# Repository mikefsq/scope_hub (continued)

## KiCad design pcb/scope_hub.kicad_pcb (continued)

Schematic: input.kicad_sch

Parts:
C206, C210: 100nF; C_0603_1608Metric; LCSC C14663
C207, C209: 100nF; C_0402_1005Metric; LCSC C1525
C208: 1uF; C_0603_1608Metric; LCSC C5199872
D8: SMBJ16CA; D_SMB; MPN SMBJ16CA; LCSC C151255
F1: 15A; Fuse_2410_6125Metric_JDT; LCSC C2994767
J11: PJ-080BH; BarrelJack_CUI_PJ-080BH_Horizontal; MPN PJ-080BH; LCSC C3094242
Q7: NCEP40T11G; PowerPAK_SO-8_Single; LCSC C182465
R115, R117: 10R; R_0603_1608Metric; LCSC C22859
R116: 1mR; R_2512_6332Metric; LCSC C5375452
U55: LM74700-Q1; SOT-23-6; MPN LM74700QDBVRQ1; LCSC C2941042
U56: INA226; TSSOP-10_3x3mm_P0.5mm; MPN INA226AIDGSR; LCSC C49851

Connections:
+3V3: C207.1, U56.1 (A1), U56.6 (VS); also elsewhere on the board
+12V: C210.1, F1.2; also elsewhere on the board
/I2C0_SCL: U56.5 (SCL); also elsewhere on the board
/I2C0_SDA: U56.2 (A0), U56.4 (SDA); also elsewhere on the board
/Input 12V/VIN_PROT: Q7.5 (D), R115.1, R116.1, U55.4 (CATHODE), U56.8 (Vbus)
/Input 12V/VIN_RAW: C206.1, C208.1, D8.1 (K), J11.1, Q7.1 (S), Q7.2 (S), Q7.3 (S), U55.3 (EN), U55.6 (ANODE)
GND: C206.2, C207.2, C210.2, D8.2 (A), J11.2, J11.3, U55.2 (GND), U56.7 (GND); also elsewhere on the board
unnamed: F1.1, R116.2, R117.1
unnamed: Q7.4 (G), U55.5 (GATE)
unnamed: C208.2, U55.1 (VCAP)
unnamed: C209.1, R115.2, U56.10 (Vin+)
unnamed: C209.2, R117.2, U56.9 (Vin-)

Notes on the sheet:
INA226 at 0x46 (A1=VS, A0=SDA)

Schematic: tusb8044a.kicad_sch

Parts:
C78: 1uF; C_0402_1005Metric; LCSC C52923
C79, C108: 10uF; C_0805_2012Metric; LCSC C15850
C80, C85: 18pF; C_0402_1005Metric; LCSC C1549
C81, C82, C88, C89, C95, C96, C102, C103, C109: 0.001uF; C_0402_1005Metric; LCSC C1523
C83, C84, C90, C91, C98, C99, C104, C105, C110: 0.01uF; C_0402_1005Metric; LCSC C15195
C86, C87, C92, C93, C94, C100, C101, C106, C107, C111: 0.1uF; C_0402_1005Metric; LCSC C1525
R43, R45, R46, R52: 1K; R_0402_1005Metric; LCSC C11702
R44: 1M; R_0402_1005Metric; LCSC C26083
R47: 9.53K; R_0402_1005Metric; LCSC C96273
R48: 10K; R_0402_1005Metric; LCSC C25744
R49: 90.9K; R_0402_1005Metric; LCSC C26989
R50, R53, R54: 4.7K; R_0402_1005Metric; LCSC C25900
R51: NOPOP; R_0402_1005Metric; not fitted
R55, R56, R57: 4.7K DNI; R_0402_1005Metric; LCSC C25900; not fitted
U21: AT24C08C; SOIC-8_3.9x4.9mm_P1.27mm; LCSC C31422
U22: TUSB8044A; QFN-64-1EP_9x9mm_P0.5mm_EP6x6mm_ThermalVias; MPN TUSB8044ARGCR; LCSC C2678041
Y2: 24MHz; Crystal_SMD_3225-4Pin_3.2x2.5mm; LCSC C362340

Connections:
+1V1: C79.1, C82.1, C84.1, C87.1, C89.1, C91.1, C93.1, C96.1, C99.1, C101.1, C103.1, C105.1, C107.1, C108.1, C109.1, C110.1, C111.1, U22.5 (VDD), U22.8 (VDD), U22.13 (VDD), U22.21 (VDD), U22.28 (VDD), U22.31 (VDD), U22.51 (VDD), U22.57 (VDD); also elsewhere on the board
+3V3: C78.1, C81.1, C83.1, C86.1, C88.1, C90.1, C92.1, C94.1, C95.1, C98.1, C100.1, C102.1, C104.1, C106.1, R51.1, R53.1, R54.1, R55.1, R56.1, R57.1, U21.8 (VCC), U22.16 (VDD33), U22.34 (VDD33), U22.52 (VDD33), U22.63 (VDD33); also elsewhere on the board
/DN4_D_N: U22.2 (USB_DM_DN1); also elsewhere on the board
/DN4_D_P: U22.1 (USB_DP_DN1); also elsewhere on the board
/DN5_D_N: U22.10 (USB_DM_DN2); also elsewhere on the board
/DN5_D_P: U22.9 (USB_DP_DN2); also elsewhere on the board
/DN6_D_N: U22.18 (USB_DM_DN3); also elsewhere on the board
/DN6_D_P: U22.17 (USB_DP_DN3); also elsewhere on the board
/DN Port 4/OVERCUR_N: U22.46 (OVERCUR1z); also elsewhere on the board
/DN Port 4/SSRX_N: U22.7 (USB_SSRXM_DN1); also elsewhere on the board
/DN Port 4/SSRX_P: U22.6 (USB_SSRXP_DN1); also elsewhere on the board
/DN Port 4/SSTX_N: U22.4 (USB_SSTXM_DN1); also elsewhere on the board
/DN Port 4/SSTX_P: U22.3 (USB_SSTXP_DN1); also elsewhere on the board
/DN Port 5/OVERCUR_N: U22.47 (OVERCUR2z); also elsewhere on the board
/DN Port 5/SSRX_N: U22.15 (USB_SSRXM_DN2); also elsewhere on the board
/DN Port 5/SSRX_P: U22.14 (USB_SSRXP_DN2); also elsewhere on the board
/DN Port 5/SSTX_N: U22.12 (USB_SSTXM_DN2); also elsewhere on the board
/DN Port 5/SSTX_P: U22.11 (USB_SSTXP_DN2); also elsewhere on the board
/DN Port 6 (5A)/OVERCUR_N: U22.44 (OVERCUR3z); also elsewhere on the board
/DN Port 6 (5A)/SSRX_N: U22.23 (USB_SSRXM_DN3); also elsewhere on the board
/DN Port 6 (5A)/SSRX_P: U22.22 (USB_SSRXP_DN3); also elsewhere on the board
/DN Port 6 (5A)/SSTX_N: U22.20 (USB_SSTXM_DN3); also elsewhere on the board
/DN Port 6 (5A)/SSTX_P: U22.19 (USB_SSTXP_DN3); also elsewhere on the board
/LB_N: U22.59 (USB_SSRXM_UP); also elsewhere on the board
/LB_P: U22.58 (USB_SSRXP_UP); also elsewhere on the board
/LC_N: U22.56 (USB_SSTXM_UP); also elsewhere on the board
/LC_P: U22.55 (USB_SSTXP_UP); also elsewhere on the board
/LNK_D_N: U22.54 (USB_DM_UP); also elsewhere on the board
/LNK_D_P: U22.53 (USB_DP_UP); also elsewhere on the board
/PICO_D_N: U22.25 (USB_DM_DN4); also elsewhere on the board
/PICO_D_P: U22.24 (USB_DP_DN4); also elsewhere on the board
/RAILS_READY: U22.50 (GRSTz); also elsewhere on the board
/TUSB8044A Hub1/OVERCUR4Z: U22.43 (OVERCUR4z)
/TUSB8044A Hub1/PWRON1_BATEN1: R55.2, U22.36 (PWRCTL1/BATEN1); also elsewhere on the board
/TUSB8044A Hub1/PWRON2_BATEN2: R56.2, U22.35 (PWRCTL2/BATEN2); also elsewhere on the board
/TUSB8044A Hub1/PWRON3_BATEN3: R57.2, U22.33 (PWRCTL3/BATEN3); also elsewhere on the board
/TUSB8044A Hub1/PWRON4_BATEN4: U22.32 (PWRCTL4/BATEN4)
/TUSB8044A Hub1/SCL_SMBCLK: R53.2, U21.6 (SCL), U22.38 (SCL/SMBCLK)
/TUSB8044A Hub1/SDA_SMBDAT: R54.2, U21.5 (SDA), U22.37 (SDA/SMBDAT)
/TUSB8044A Hub1/TEST_TRSTZ: R50.1, U22.49 (TEST)
/TUSB8044A Hub1/USB_R1: R47.1, U22.64 (USB_R1)
/TUSB8044A Hub1/USB_SSRXM_DN4: U22.30 (USB_SSRXM_DN4)
/TUSB8044A Hub1/USB_SSRXP_DN4: U22.29 (USB_SSRXP_DN4)
/TUSB8044A Hub1/USB_SSTXM_DN4: U22.27 (USB_SSTXM_DN4)
/TUSB8044A Hub1/USB_SSTXP_DN4: U22.26 (USB_SSTXP_DN4)
/TUSB8044A Hub1/USB_VBUS: R48.1, R49.1, U22.48 (USB_VBUS)
/TUSB8044A Hub1/XI: C85.1, R44.2, U22.62 (XI), Y2.3
/TUSB8044A Hub1/XO: C80.1, R44.1, U22.61 (XO), Y2.1
/UP_VBUS: R49.2; also elsewhere on the board
GND: C78.2, C79.2, C80.2, C81.2, C82.2, C83.2, C84.2, C85.2, C86.2, C87.2, C88.2, C89.2, C90.2, C91.2, C92.2, C93.2, C94.2, C95.2, C96.2, C98.2, C99.2, C100.2, C101.2, C102.2, C103.2, C104.2, C105.2, C106.2, C107.2, C108.2, C109.2, C110.2, C111.2, R43.2, R45.2, R46.2, R47.2, R48.2, R50.2, R52.2, U21.4 (GND), U22.65 (VSS), Y2.2 (G), Y2.4 (G); also elsewhere on the board
unnamed: R43.1, U21.1 (A0)
unnamed: R45.1, U21.2 (A1)
unnamed: R46.1, U21.3 (A2)
unnamed: R51.2, R52.1, U21.7 (WP)

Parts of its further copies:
C5: 1uF; C_0402_1005Metric; LCSC C52923
C6, C35: 10uF; C_0805_2012Metric; LCSC C15850
C7, C12: 18pF; C_0402_1005Metric; LCSC C1549
C8, C9, C15, C16, C22, C23, C29, C30, C36: 0.001uF; C_0402_1005Metric; LCSC C1523
C10, C11, C17, C18, C25, C26, C31, C32, C37: 0.01uF; C_0402_1005Metric; LCSC C15195
C13, C14, C19, C20, C21, C27, C28, C33, C34, C38: 0.1uF; C_0402_1005Metric; LCSC C1525
R1, R3, R4, R10: 1K; R_0402_1005Metric; LCSC C11702
R2: 1M; R_0402_1005Metric; LCSC C26083
R5: 9.53K; R_0402_1005Metric; LCSC C96273
R6: 10K; R_0402_1005Metric; LCSC C25744
R7: 90.9K; R_0402_1005Metric; LCSC C26989
R8, R11, R12: 4.7K; R_0402_1005Metric; LCSC C25900
R9: NOPOP; R_0402_1005Metric; not fitted
R13, R14, R15: 4.7K DNI; R_0402_1005Metric; LCSC C25900; not fitted
U1: AT24C08C; SOIC-8_3.9x4.9mm_P1.27mm; LCSC C31422
U2: TUSB8044A; QFN-64-1EP_9x9mm_P0.5mm_EP6x6mm_ThermalVias; MPN TUSB8044ARGCR; LCSC C2678041
Y1: 24MHz; Crystal_SMD_3225-4Pin_3.2x2.5mm; LCSC C362340

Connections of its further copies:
+1V1: C6.1, C9.1, C11.1, C14.1, C16.1, C18.1, C20.1, C23.1, C26.1, C28.1, C30.1, C32.1, C34.1, C35.1, C36.1, C37.1, C38.1, U2.5 (VDD), U2.8 (VDD), U2.13 (VDD), U2.21 (VDD), U2.28 (VDD), U2.31 (VDD), U2.51 (VDD), U2.57 (VDD); also elsewhere on the board
+3V3: C5.1, C8.1, C10.1, C13.1, C15.1, C17.1, C19.1, C21.1, C22.1, C25.1, C27.1, C29.1, C31.1, C33.1, R9.1, R11.1, R12.1, R13.1, R14.1, R15.1, U1.8 (VCC), U2.16 (VDD33), U2.34 (VDD33), U2.52 (VDD33), U2.63 (VDD33); also elsewhere on the board
/DN1_D_N: U2.2 (USB_DM_DN1); also elsewhere on the board
/DN1_D_P: U2.1 (USB_DP_DN1); also elsewhere on the board
/DN2_D_N: U2.10 (USB_DM_DN2); also elsewhere on the board
/DN2_D_P: U2.9 (USB_DP_DN2); also elsewhere on the board
/DN3_D_N: U2.18 (USB_DM_DN3); also elsewhere on the board
/DN3_D_P: U2.17 (USB_DP_DN3); also elsewhere on the board
/DN Port 1/OVERCUR_N: U2.46 (OVERCUR1z); also elsewhere on the board
/DN Port 1/SSRX_N: U2.7 (USB_SSRXM_DN1); also elsewhere on the board
/DN Port 1/SSRX_P: U2.6 (USB_SSRXP_DN1); also elsewhere on the board
/DN Port 1/SSTX_N: U2.4 (USB_SSTXM_DN1); also elsewhere on the board
/DN Port 1/SSTX_P: U2.3 (USB_SSTXP_DN1); also elsewhere on the board
/DN Port 2/OVERCUR_N: U2.47 (OVERCUR2z); also elsewhere on the board
/DN Port 2/SSRX_N: U2.15 (USB_SSRXM_DN2); also elsewhere on the board
/DN Port 2/SSRX_P: U2.14 (USB_SSRXP_DN2); also elsewhere on the board
/DN Port 2/SSTX_N: U2.12 (USB_SSTXM_DN2); also elsewhere on the board
/DN Port 2/SSTX_P: U2.11 (USB_SSTXP_DN2); also elsewhere on the board
/DN Port 3/OVERCUR_N: U2.44 (OVERCUR3z); also elsewhere on the board
/DN Port 3/SSRX_N: U2.23 (USB_SSRXM_DN3); also elsewhere on the board
/DN Port 3/SSRX_P: U2.22 (USB_SSRXP_DN3); also elsewhere on the board
/DN Port 3/SSTX_N: U2.20 (USB_SSTXM_DN3); also elsewhere on the board
/DN Port 3/SSTX_P: U2.19 (USB_SSTXP_DN3); also elsewhere on the board
/LA_N: U2.27 (USB_SSTXM_DN4); also elsewhere on the board
/LA_P: U2.26 (USB_SSTXP_DN4); also elsewhere on the board
/LD_N: U2.30 (USB_SSRXM_DN4); also elsewhere on the board
/LD_P: U2.29 (USB_SSRXP_DN4); also elsewhere on the board
/LNK_D_N: U2.25 (USB_DM_DN4); also elsewhere on the board
/LNK_D_P: U2.24 (USB_DP_DN4); also elsewhere on the board
/RAILS_READY: U2.50 (GRSTz); also elsewhere on the board
/SCL_SMBCLK: R11.2, U1.6 (SCL), U2.38 (SCL/SMBCLK)
/SDA_SMBDAT: R12.2, U1.5 (SDA), U2.37 (SDA/SMBDAT)
/TUSB8044A Hub/OVERCUR4Z: U2.43 (OVERCUR4z)
/TUSB8044A Hub/PWRON1_BATEN1: R13.2, U2.36 (PWRCTL1/BATEN1); also elsewhere on the board
/TUSB8044A Hub/PWRON2_BATEN2: R14.2, U2.35 (PWRCTL2/BATEN2); also elsewhere on the board
/TUSB8044A Hub/PWRON3_BATEN3: R15.2, U2.33 (PWRCTL3/BATEN3); also elsewhere on the board
/TUSB8044A Hub/PWRON4_BATEN4: U2.32 (PWRCTL4/BATEN4)
/TUSB8044A Hub/TEST_TRSTZ: R8.1, U2.49 (TEST)
/TUSB8044A Hub/USB_R1: R5.1, U2.64 (USB_R1)
/TUSB8044A Hub/USB_VBUS: R6.1, R7.1, U2.48 (USB_VBUS)
/TUSB8044A Hub/XI: C12.1, R2.2, U2.62 (XI), Y1.3
/TUSB8044A Hub/XO: C7.1, R2.1, U2.61 (XO), Y1.1
/UP_D_N: U2.54 (USB_DM_UP); also elsewhere on the board
/UP_D_P: U2.53 (USB_DP_UP); also elsewhere on the board
/UP_SSRX_N: U2.59 (USB_SSRXM_UP); also elsewhere on the board
/UP_SSRX_P: U2.58 (USB_SSRXP_UP); also elsewhere on the board
/UP_SSTX_N: U2.56 (USB_SSTXM_UP); also elsewhere on the board
/UP_SSTX_P: U2.55 (USB_SSTXP_UP); also elsewhere on the board
/UP_VBUS: R7.2; also elsewhere on the board
GND: C5.2, C6.2, C7.2, C8.2, C9.2, C10.2, C11.2, C12.2, C13.2, C14.2, C15.2, C16.2, C17.2, C18.2, C19.2, C20.2, C21.2, C22.2, C23.2, C25.2, C26.2, C27.2, C28.2, C29.2, C30.2, C31.2, C32.2, C33.2, C34.2, C35.2, C36.2, C37.2, C38.2, R1.2, R3.2, R4.2, R5.2, R6.2, R8.2, R10.2, U1.4 (GND), U2.65 (VSS), Y1.2 (G), Y1.4 (G); also elsewhere on the board
unnamed: R1.1, U1.1 (A0)
unnamed: R3.1, U1.2 (A1)
unnamed: R4.1, U1.3 (A2)
unnamed: R9.2, R10.1, U1.7 (WP)

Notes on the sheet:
24 MHz CLOCK
RAIL FILTERING AND DECOUPLING
UPSTREAM VBUS DETECT (divider good to 11.4V)
REF RESISTOR / RESET / TEST
hub HID-to-I2C master
OPTIONAL EEPROM CIRCUITRY

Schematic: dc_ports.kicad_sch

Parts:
C211, C212, C213, C214, C215, C216, C217, C218: 10uF; C_1210_3225Metric; LCSC C386166
C219, C220, C221, C222, C223, C224: 100nF; C_0603_1608Metric; LCSC C14663
C233: 100nF; C_0402_1005Metric; LCSC C1525
D9, D10, D11, D12, D13, D14: LED red; LED_0603_1608Metric; LCSC C2286
J12, J13, J14, J15, J16, J17: 2 Conductors, 3 Contacts; BarrelJack_CUI_PJ-063AH_Horizontal; MPN PJ-063AH; LCSC C22434582
R118, R119: 2.2K; R_0402_1005Metric; LCSC C25879
R120: 10 mOhms; RC2010N_VIS; MPN LRAM20DFER010; LCSC C22470460
R121, R122, R123, R124, R125: 20 mOhms; R_1206_3216Metric; MPN FMF06FTHR020-LH; LCSC C371097
R126, R127, R128, R129, R130, R131: 330; R_0402_1005Metric; LCSC C25104
U57: PCA9685BS; QFN-28-1EP_6x6mm_P0.65mm_EP4.25x4.25mm; MPN PCA9685BS,118; LCSC C5191634

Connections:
+3V3: C233.2, D9.2 (A), D10.2 (A), D11.2 (A), D12.2 (A), D13.2 (A), D14.2 (A), R118.1, R119.1, U57.21 (A5), U57.25 (VDD); also elsewhere on the board
+12V: C211.1, C212.1; also elsewhere on the board
/DC Ports/Vout0: C213.1, C219.1, J12.1, R120.2; also elsewhere on the board
/DC Ports/Vout0_EN: U57.3 (LED0); also elsewhere on the board
/DC Ports/Vout0_HS: R120.1; also elsewhere on the board
/DC Ports/Vout0_LED: R126.2, U57.4 (LED1)
/DC Ports/Vout1: C214.1, C220.1, J13.1, R121.2; also elsewhere on the board
/DC Ports/Vout1_EN: U57.5 (LED2); also elsewhere on the board
/DC Ports/Vout1_HS: R121.1; also elsewhere on the board
/DC Ports/Vout1_LED: R127.2, U57.6 (LED3)
/DC Ports/Vout2: C215.1, C221.1, J14.1, R122.2; also elsewhere on the board
/DC Ports/Vout2_EN: U57.7 (LED4); also elsewhere on the board
/DC Ports/Vout2_HS: R122.1; also elsewhere on the board
/DC Ports/Vout2_LED: R128.2, U57.8 (LED5)
/DC Ports/Vout3: C216.1, C222.1, J15.1, R123.2; also elsewhere on the board
/DC Ports/Vout3_EN: U57.9 (LED6); also elsewhere on the board
/DC Ports/Vout3_HS: R123.1; also elsewhere on the board
/DC Ports/Vout3_LED: R129.2, U57.10 (LED7)
/DC Ports/Vout4: C217.1, C223.1, J16.1, R124.2; also elsewhere on the board
/DC Ports/Vout4_EN: U57.12 (LED8); also elsewhere on the board
/DC Ports/Vout4_HS: R124.1; also elsewhere on the board
/DC Ports/Vout4_LED: R130.2, U57.13 (LED9)
/DC Ports/Vout5: C218.1, C224.1, J17.1, R125.2; also elsewhere on the board
/DC Ports/Vout5_EN: U57.14 (LED10); also elsewhere on the board
/DC Ports/Vout5_HS: R125.1; also elsewhere on the board
/DC Ports/Vout5_LED: R131.2, U57.15 (LED11)
/I2C0_SCL: R118.2, U57.23 (SCL); also elsewhere on the board
/I2C0_SDA: R119.2, U57.24 (SDA); also elsewhere on the board
/USBLED_12: U57.16 (LED12); also elsewhere on the board
/USBLED_34: U57.17 (LED13); also elsewhere on the board
/USBLED_56: U57.18 (LED14); also elsewhere on the board
/USBLED_UP: U57.19 (LED15); also elsewhere on the board
GND: C211.2, C212.2, C213.2, C214.2, C215.2, C216.2, C217.2, C218.2, C219.2, C220.2, C221.2, C222.2, C223.2, C224.2, C233.1, J12.2, J12.3, J13.2, J13.3, J14.2, J14.3, J15.2, J15.3, J16.2, J16.3, J17.2, J17.3, U57.1 (A3), U57.2 (A4), U57.11 (VSS), U57.20 (~OE), U57.22 (EXTCLK), U57.26 (A0), U57.27 (A1), U57.28 (A2), U57.29 (VSS); also elsewhere on the board
unnamed: D9.1 (K), R126.1
unnamed: D10.1 (K), R127.1
unnamed: D11.1 (K), R128.1
unnamed: D12.1 (K), R129.1
unnamed: D13.1 (K), R130.1
unnamed: D14.1 (K), R131.1

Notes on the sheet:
AUX2
DEW2
Focuser
DEW1
0x42
TEC
I2c Address = 0x40 + A[5:0]
C194/C195: 25 V X5R 0805, place at the switch group
0x40
0x45
All Call Address 0x70
0x41
0x44
AUX1
0x43

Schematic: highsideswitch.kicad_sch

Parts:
R137: 499R; R_0402_1005Metric; LCSC C4125
U67: High Side N-Channel On/Off; PWP0014F_N; MPN TPS1H100AQPWPRQ1; LCSC C478465

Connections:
+12V: U67.8 (VS), U67.9 (VS), U67.10 (VS); also elsewhere on the board
/DC Ports/Vout4_EN: U67.3 (IN); also elsewhere on the board
/DC Ports/Vout4_HS: U67.5 (OUT), U67.6 (OUT), U67.7 (OUT); also elsewhere on the board
/DC Ports/Vout4_ST: U67.14 (ST_N)
GND: R137.2, U67.2 (GND), U67.12 (DIAG_EN), U67.15 (PAD); also elsewhere on the board
unnamed: R137.1, U67.13 (CL)

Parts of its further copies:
R133, R134, R135, R136, R138: 499R; R_0402_1005Metric; LCSC C4125
U63, U64, U65, U66, U68: High Side N-Channel On/Off; PWP0014F_N; MPN TPS1H100AQPWPRQ1; LCSC C478465

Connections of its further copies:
+12V: U63.8 (VS), U63.9 (VS), U63.10 (VS), U64.8 (VS), U64.9 (VS), U64.10 (VS), U65.8 (VS), U65.9 (VS), U65.10 (VS), U66.8 (VS), U66.9 (VS), U66.10 (VS), U68.8 (VS), U68.9 (VS), U68.10 (VS); also elsewhere on the board
/DC Ports/Vout0_EN: U63.3 (IN); also elsewhere on the board
/DC Ports/Vout0_HS: U63.5 (OUT), U63.6 (OUT), U63.7 (OUT); also elsewhere on the board
/DC Ports/Vout0_ST: U63.14 (ST_N)
/DC Ports/Vout1_EN: U64.3 (IN); also elsewhere on the board
/DC Ports/Vout1_HS: U64.5 (OUT), U64.6 (OUT), U64.7 (OUT); also elsewhere on the board
/DC Ports/Vout1_ST: U64.14 (ST_N)
/DC Ports/Vout2_EN: U65.3 (IN); also elsewhere on the board
/DC Ports/Vout2_HS: U65.5 (OUT), U65.6 (OUT), U65.7 (OUT); also elsewhere on the board
/DC Ports/Vout2_ST: U65.14 (ST_N)
/DC Ports/Vout3_EN: U66.3 (IN); also elsewhere on the board
/DC Ports/Vout3_HS: U66.5 (OUT), U66.6 (OUT), U66.7 (OUT); also elsewhere on the board
/DC Ports/Vout3_ST: U66.14 (ST_N)
/DC Ports/Vout5_EN: U68.3 (IN); also elsewhere on the board
/DC Ports/Vout5_HS: U68.5 (OUT), U68.6 (OUT), U68.7 (OUT); also elsewhere on the board
/DC Ports/Vout5_ST: U68.14 (ST_N)
GND: R133.2, R134.2, R135.2, R136.2, R138.2, U63.2 (GND), U63.12 (DIAG_EN), U63.15 (PAD), U64.2 (GND), U64.12 (DIAG_EN), U64.15 (PAD), U65.2 (GND), U65.12 (DIAG_EN), U65.15 (PAD), U66.2 (GND), U66.12 (DIAG_EN), U66.15 (PAD), U68.2 (GND), U68.12 (DIAG_EN), U68.15 (PAD); also elsewhere on the board
unnamed: R133.1, U63.13 (CL)
unnamed: R134.1, U64.13 (CL)
unnamed: R135.1, U65.13 (CL)
unnamed: R136.1, U66.13 (CL)
unnamed: R138.1, U68.13 (CL)

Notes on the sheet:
DIAG_EN tied to GND (datasheet: connect to GND if unused) - this disables the ST status output; per-port INA226 monitors are the diagnostics.
CL must never float (TPS1H100-Q1, SLVSCM2D): I_limit = 1.233 V x 2000 / R_CL. Fitted 499R = 4.94 A. 620R = 3.98 A, 820R = 3.0 A. CL to GND = internal ~10 A limit.

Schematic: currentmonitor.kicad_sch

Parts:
C232: 0.1uF; C_0402_1005Metric; LCSC C1525
U69: INA226; TSSOP-10_3x3mm_P0.5mm; MPN INA226AIDGSR; LCSC C49851

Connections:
+3V3: C232.1, U69.2 (A0), U69.6 (VS); also elsewhere on the board
/DC Ports/Vout1: U69.9 (Vin-); also elsewhere on the board
/DC Ports/Vout1_HS: U69.8 (Vbus), U69.10 (Vin+); also elsewhere on the board
/I2C0_SCL: U69.5 (SCL); also elsewhere on the board
/I2C0_SDA: U69.4 (SDA); also elsewhere on the board
GND: C232.2, U69.1 (A1), U69.7 (GND); also elsewhere on the board

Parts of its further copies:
C119, C228, C229, C230, C231: 0.1uF; C_0402_1005Metric; LCSC C1525
U27, U59, U60, U61, U62: INA226; TSSOP-10_3x3mm_P0.5mm; MPN INA226AIDGSR; LCSC C49851

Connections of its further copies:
+3V3: C119.1, C228.1, C229.1, C230.1, C231.1, U27.6 (VS), U59.6 (VS), U60.6 (VS), U61.1 (A1), U61.6 (VS), U62.1 (A1), U62.2 (A0), U62.6 (VS); also elsewhere on the board
/DC Ports/Vout0: U27.9 (Vin-); also elsewhere on the board
/DC Ports/Vout0_HS: U27.8 (Vbus), U27.10 (Vin+); also elsewhere on the board
/DC Ports/Vout2: U59.9 (Vin-); also elsewhere on the board
/DC Ports/Vout2_HS: U59.8 (Vbus), U59.10 (Vin+); also elsewhere on the board
/DC Ports/Vout3: U60.9 (Vin-); also elsewhere on the board
/DC Ports/Vout3_HS: U60.8 (Vbus), U60.10 (Vin+); also elsewhere on the board
/DC Ports/Vout4: U61.9 (Vin-); also elsewhere on the board
/DC Ports/Vout4_HS: U61.8 (Vbus), U61.10 (Vin+); also elsewhere on the board
/DC Ports/Vout5: U62.9 (Vin-); also elsewhere on the board
/DC Ports/Vout5_HS: U62.8 (Vbus), U62.10 (Vin+); also elsewhere on the board
/I2C0_SCL: U27.5 (SCL), U59.5 (SCL), U60.2 (A0), U60.5 (SCL), U61.5 (SCL), U62.5 (SCL); also elsewhere on the board
/I2C0_SDA: U27.4 (SDA), U59.2 (A0), U59.4 (SDA), U60.4 (SDA), U61.4 (SDA), U62.4 (SDA); also elsewhere on the board
GND: C119.2, C228.2, C229.2, C230.2, C231.2, U27.1 (A1), U27.2 (A0), U27.7 (GND), U59.1 (A1), U59.7 (GND), U60.1 (A1), U60.7 (GND), U61.2 (A0), U61.7 (GND), U62.7 (GND); also elsewhere on the board

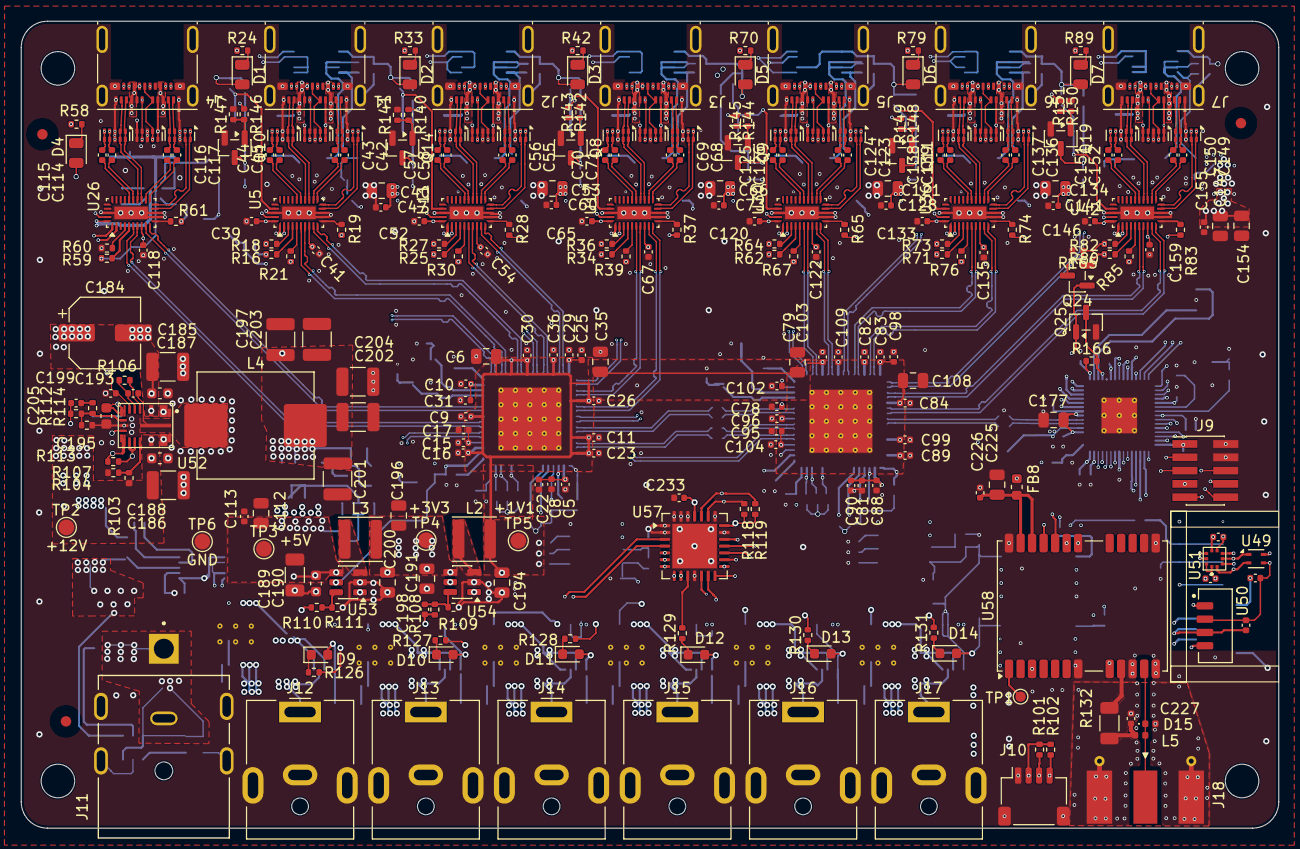
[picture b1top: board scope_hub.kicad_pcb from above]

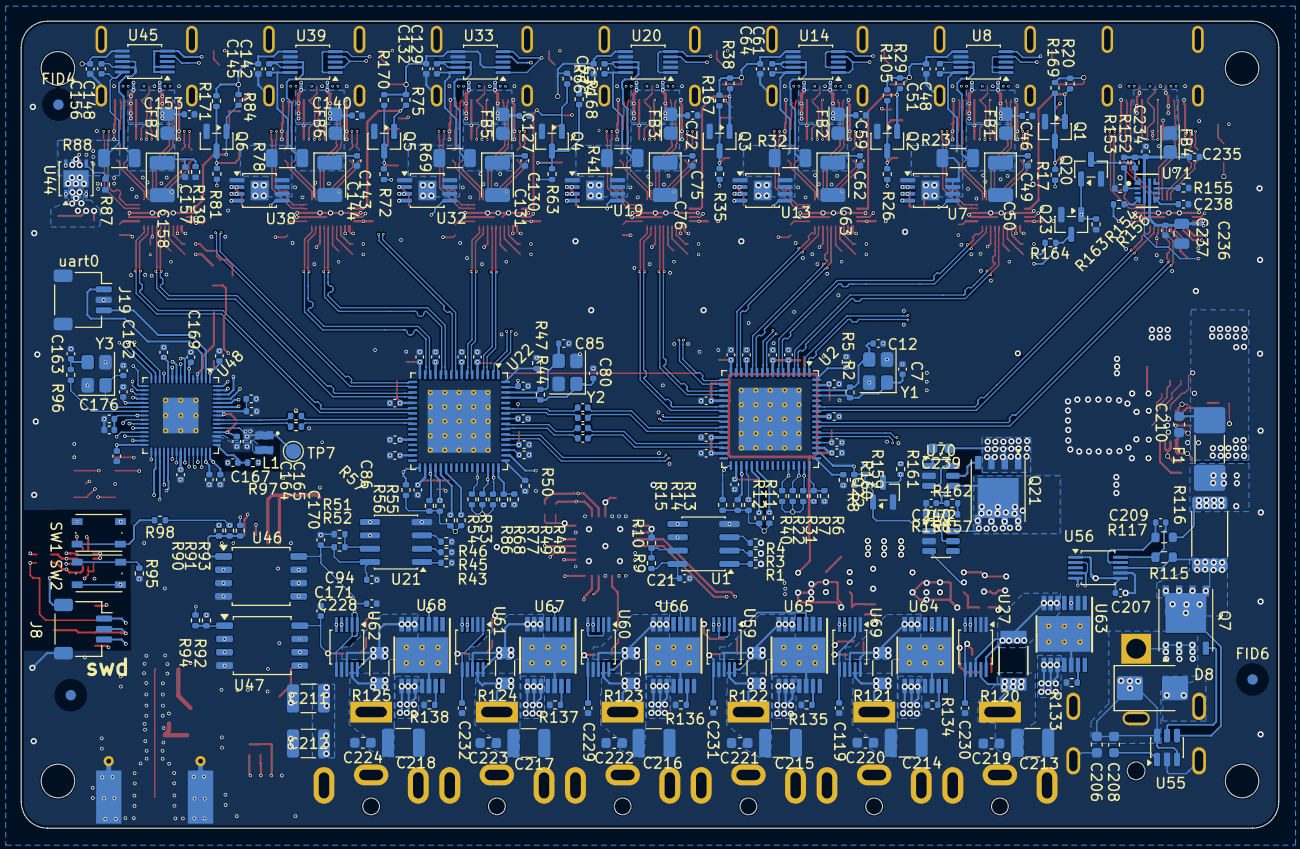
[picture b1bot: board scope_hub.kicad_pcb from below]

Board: 10 copper layers, 120.0 x 77.0 mm, 569 parts (284 on the bottom side), 387 nets.

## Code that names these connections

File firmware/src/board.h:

// Pin and I2C address map for the scope_hub board
#pragma once

#include <stdint.h>

#define BOARD_TABLE static const __attribute__((unused))

// I2C0: power monitoring and the PCA9685
#define I2C0_SDA_PIN 4
#define I2C0_SCL_PIN 5
#define I2C0_BAUD 400000

// I2C1: environment sensors, GPS DDC, Qwiic J10 and display header J9
#define I2C1_SDA_PIN 6
#define I2C1_SCL_PIN 7
#define I2C1_BAUD 100000

// GPS U58 NEO-M9N on UART1, 38400 8N1 by default
#define GPS_TX_PIN 20
#define GPS_RX_PIN 21
#define GPS_PPS_PIN 22
#define GPS_RESET_N_PIN 23
#define GPS_BAUD 38400

// Display header J9 (SPI0 plus I2C1)
#define DISP_GPIO15_PIN 15
#define DISP_MISO_PIN 16
#define DISP_CS_PIN 17
#define DISP_SCLK_PIN 18
#define DISP_MOSI_PIN 19

// Q25 drain with a 10k pull-up
#define LOCAL_5V_GOOD_PIN 2

// USB-C downstream ports
// ATTACH_N: low when a device is plugged in
// INHIBIT: high forces the port's VBUS switch off
#define USB_PORTS 6
BOARD_TABLE uint8_t usb_attach_n_pin[USB_PORTS] = {14, 13, 12, 11, 10, 9};
BOARD_TABLE uint8_t usb_inhibit_pin[USB_PORTS] = {29, 28, 27, 26, 25, 24};

// INA226 7-bit addresses and shunt resistances.
#define INA_IN_ADDR 0x46
#define INA_IN_SHUNT_OHM 0.001f

#define DC_PORTS 6
BOARD_TABLE uint8_t dc_ina_addr[DC_PORTS] = {0x40, 0x41, 0x42, 0x43, 0x44, 0x45};
BOARD_TABLE float dc_shunt_ohm[DC_PORTS] = {0.010f, 0.020f, 0.020f, 0.020f, 0.020f, 0.020f};

BOARD_TABLE uint8_t usb_ina_addr[USB_PORTS] = {0x4A, 0x4B, 0x4C, 0x4D, 0x4E, 0x4F};
BOARD_TABLE float usb_shunt_ohm[USB_PORTS] = {0.010f, 0.010f, 0.010f, 0.010f, 0.010f, 0.005f};

// PCA9685 U57 (A5 high, A4..A0 low)
#define PCA9685_ADDR 0x60
// DC port n: channel 2n drives the TPS1H100 IN (high = on)
// channel 2n+1 sinks the port LED (low = lit)
#define PCA_DC_EN_CH(n) (2 * (n))
#define PCA_DC_LED_CH(n) (2 * (n) + 1)
#define PCA_USBLED_12_CH 12
#define PCA_USBLED_34_CH 13
#define PCA_USBLED_56_CH 14
#define PCA_USBLED_UP_CH 15

// Environment sensors on I2C1.
#define SHT45_ADDR 0x44
#define VEML7700_ADDR 0x10
#define BMP581_ADDR 0x46
#define BMP581_ADDR_ALT 0x47
#define NEO_M9N_ADDR 0x42
